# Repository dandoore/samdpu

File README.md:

# SAM Coupé Disk Protector Unit

The Disk Protector Unit or DPU for short is a small circuit designed to cure corruption of disks whenever the SAM Coupé is reset or turned on with a disk in the floppy drive.

**Details**

The problem is caused when the 8 MHz clock generated by the ASIC is halted during reset, this causes the floppy disk controller to go out of control since it needs the 8 MHz clock all the time.

All that the DPU does is generate a constant 8 MHz clock to replace the ASIC's 8 MHz clock.

Note: you will require basic soldering and track cutting skills to install this modification, if you are uncomfortable doing it then seek assistance.

Consult the following guide for opening and closing your SAM: https://www.worldofsam.org/products/disassembly-and-reassembly 

Before fitting the DPU you must cut the ASIC’s 8 MHz clock PCB track at the place shown below, it also shows the places where to solder the 5V, GND/0V and 8 MHz clock wires.

Use double-sided Foampads to mount the DPU on top of the ASIC.

(C) 1998 Edwin Blink, PCB & Instructions by Dan Dooré 2021/2024

**Schematic**

**Photos**

Before installation

After installation
Note: Newer PCB has solder points in different locations but no functional change.

Newer PCB

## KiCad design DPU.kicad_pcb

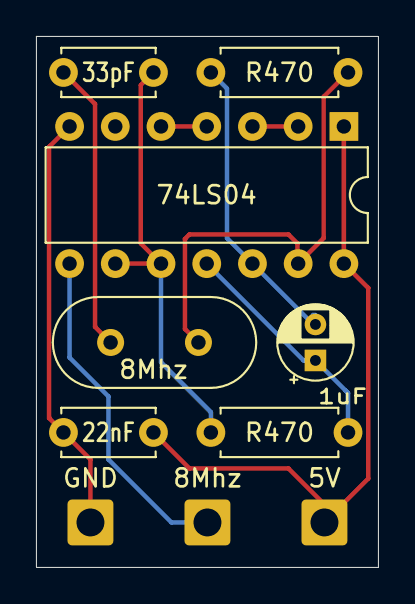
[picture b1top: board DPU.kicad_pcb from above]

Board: 2 copper layers, 19.0 x 29.5 mm, 10 parts (0 on the bottom side), 10 nets.

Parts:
5V, 8Mhz: MountingHole_Pad; SolderWire-0.75sqmm_1x01_D1.25mm_OD2.3mm
C1: 33pF; C_Disc_D5.0mm_W2.5mm_P5.00mm
C2: 1uF; CP_Radial_D4.0mm_P2.00mm
C3: 22nF; C_Disc_D5.0mm_W2.5mm_P5.00mm
GND: MountingHole_Pad; SolderWire-0.75sqmm_1x01_D1.25mm_OD2.3mm
R1, R2: R470; R_Axial_DIN0207_L6.3mm_D2.5mm_P7.62mm_Horizontal
U1: 74LS04; DIP-14_W7.62mm
Y1: 8Mhz; Crystal_HC49-U_Vertical

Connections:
unnamed: 8Mhz.1, U1.8
unnamed: C1.1, R2.1, U1.9, U1.10
unnamed: C1.2, Y1.2
unnamed: C2.1, R2.2, U1.11
unnamed: C2.2, R1.1, U1.12
unnamed: R1.2, U1.13, Y1.1
unnamed: U1.2, U1.3
unnamed: U1.4, U1.5
unnamed: C3.2, GND.1, U1.7 (GND)
unnamed: 5V.1, C3.1, U1.1, U1.14 (VCC)

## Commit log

2021-04-01 Initial Upload
2024-11-28 Updated PCB (Kicad 8.0)
    Smaller PCB for easier mounting inside case and reduced wire holes to sensible size.
2024-11-28 Updated gerbers
2024-11-28 Update README.md for new PCB
2024-11-28 Moved silkscreen text to bottom
2024-12-19 Update README.md with new PCB image

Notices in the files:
DPU.kicad_pcb:
SAM DPU (C) 1998
